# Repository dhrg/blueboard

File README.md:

blueboard
=========

This repository contains Eagle design files of 
- Blueboard v1.0 (Arduino pin compatible with ADXL chip and jumpers to enable Bluetooth and ADXL) 
- Blueboard v1.1 (Arduino pin compatible smaller variant without ADXL just enabled Bluetooth module)

License Information
-------------------
The hardware design files are released under [Creative Commons Attribution-ShareAlike 3.0 Unported (CC BY-SA 3.0)](https://creativecommons.org/licenses/by-sa/3.0/deed.en_US).

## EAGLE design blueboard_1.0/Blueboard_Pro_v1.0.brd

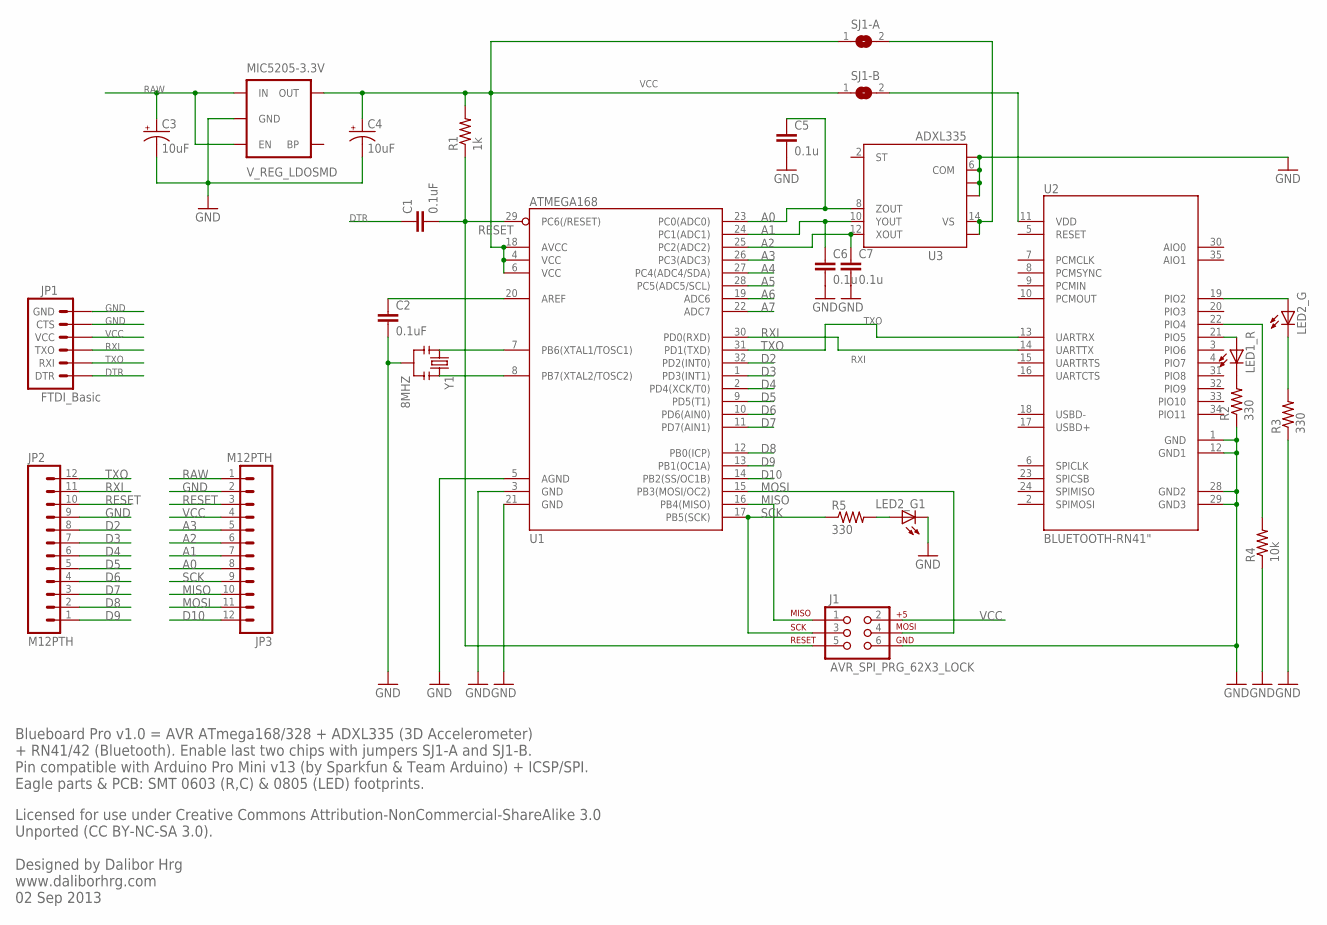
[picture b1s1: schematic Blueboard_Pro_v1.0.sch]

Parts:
C1, C2: 0.1uF; 0603-CAP
C3, C4: 10uF; EIA3216
C5, C6, C7: 0.1u; 0603-CAP
J1: AVR_SPI_PRG_62X3_LOCK; 2X3_LOCK
JP1: FTDI_Basic; 1X06
JP2, JP3: M12PTH; 1X12
LED1_R, LED2_G, LED2_G1: LEDCHIP-LED0805; CHIP-LED0805
MIC5205-3.3V: V_REG_LDOSMD; SOT23-5
R1: 1k; 0603-RES
R2, R3, R5: 330; 0603-RES
R4: 10k; 0603-RES
SJ1-A, SJ1-B: SJ
U1: ATMEGA168; TQFP32-08
U2: BLUETOOTH-RN41"; RN41
U3: ADXL335; LFCSP-16
Y1: 8MHZ; RESONATOR-SMD

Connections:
A0: C5.1, JP3.8, U1.23 (PC0(ADC0)), U3.8 (ZOUT)
A1: C6.1, JP3.7, U1.24 (PC1(ADC1)), U3.10 (YOUT)
A2: C7.1, JP3.6, U1.25 (PC2(ADC2)), U3.12 (XOUT)
A3: JP3.5, U1.26 (PC3(ADC3))
A4: U1.27 (PC4(ADC4/SDA))
A5: U1.28 (PC5(ADC5/SCL))
A6: U1.19 (ADC6)
A7: U1.22 (ADC7)
D2: JP2.8, U1.32 (PD2(INT0))
D3: JP2.7, U1.1 (PD3(INT1))
D4: JP2.6, U1.2 (PD4(XCK/T0))
D5: JP2.5, U1.9 (PD5(T1))
D6: JP2.4, U1.10 (PD6(AIN0))
D7: JP2.3, U1.11 (PD7(AIN1))
D8: JP2.2, U1.12 (PB0(ICP))
D9: JP2.1, U1.13 (PB1(OC1A))
D10: JP3.12, U1.14 (PB2(SS/OC1B))
DTR: C1.1, JP1.1 (DTR)
GND: C2.2, C3.C (-), C4.C (-), C5.2, C6.2, C7.2, J1.6, JP1.5 (CTS), JP1.6 (GND), JP2.9, JP3.2, LED2_G1.C, MIC5205-3.3V.2 (GND), R2.1, R3.1, R4.1, U1.3 (GND), U1.5 (AGND), U1.21 (GND), U2.1 (GND), U2.12 (GND1), U2.28 (GND2), U2.29 (GND3), U3.3 (COM), U3.5 (COM), U3.6 (COM), U3.7 (COM), Y1.2
MISO: J1.1, JP3.10, U1.16 (PB4(MISO))
MOSI: J1.4, JP3.11, U1.15 (PB3(MOSI/OC2))
unnamed: LED2_G1.A, R5.2
unnamed: SJ1-A.2, U3.14 (VS), U3.15 (VS)
unnamed: SJ1-B.2, U2.11 (VDD)
unnamed: U1.7 (PB6(XTAL1/TOSC1)), Y1.1
unnamed: U1.8 (PB7(XTAL2/TOSC2)), Y1.3
unnamed: C2.1, U1.20 (AREF)
unnamed: LED1_R.A, U2.21 (PIO5)
unnamed: LED1_R.C, R2.2
unnamed: LED2_G.C, R3.2
unnamed: LED2_G.A, U2.19 (PIO2)
unnamed: R4.2, U2.22 (PIO4)
RAW: C3.A (+), JP3.1, MIC5205-3.3V.1 (IN), MIC5205-3.3V.3 (EN)
RESET: C1.2, J1.5, JP2.10, JP3.3, R1.1, U1.29 (PC6(/RESET))
RXI: JP1.3 (TXO), JP2.11, U1.30 (PD0(RXD)), U2.14 (UARTTX)
SCK: J1.3, JP3.9, R5.1, U1.17 (PB5(SCK))
TXO: JP1.2 (RXI), JP2.12, U1.31 (PD1(TXD)), U2.13 (UARTRX)
VCC: C4.A (+), J1.2, JP1.4 (VCC), JP3.4, MIC5205-3.3V.5 (OUT), R1.2, SJ1-A.1, SJ1-B.1, U1.4 (VCC), U1.6 (VCC), U1.18 (AVCC)

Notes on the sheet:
Licensed for use under Creative Commons Attribution-NonCommercial-ShareAlike 3.0 Unported (CC BY-NC-SA 3.0). Designed by Dalibor Hrg www.daliborhrg.com 02 Sep 2013
Blueboard Pro v1.0 = AVR ATmega168/328 + ADXL335 (3D Accelerometer) + RN41/42 (Bluetooth). Enable last two chips with jumpers SJ1-A and SJ1-B. Pin compatible with Arduino Pro Mini v13 (by Sparkfun & Team Arduino) + ICSP/SPI. Eagle parts & PCB: SMT 0603 (R,C) & 0805 (LED) footprints.

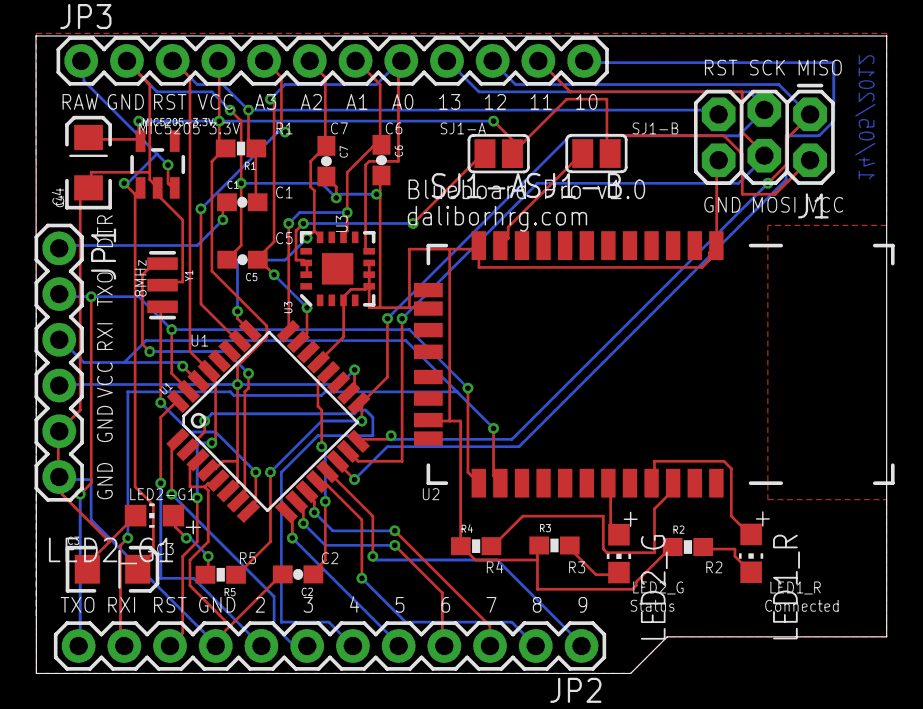
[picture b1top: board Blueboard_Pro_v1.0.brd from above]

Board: 2 copper layers, 47.3 x 35.4 mm, 26 parts (0 on the bottom side), 34 nets.

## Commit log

2016-07-03 Create filetest
2016-07-03 Added v1.0 and v1.1
2016-07-03 Added images of v1.0 and v1.1

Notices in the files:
parts and their libraries:
SparkFun-RF: Licensing: CC v3.0 Share-Alike You are welcome to use this library for commercial purposes.
